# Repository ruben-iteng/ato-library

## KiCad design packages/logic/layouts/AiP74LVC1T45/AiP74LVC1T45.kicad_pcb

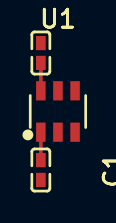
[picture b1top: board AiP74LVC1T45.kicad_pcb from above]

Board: 2 copper layers, 3 parts (0 on the bottom side), 3 nets.

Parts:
C1, C2: 100nF ±10% 16V X7R; C0402-b3ef17
U1: SOT-23-6_L2.9-W1.6-P0.95-LS2.8-BL-d2c740

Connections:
gnd: C1.2, C2.2, U1.2
hv: C1.1, U1.1
hv-1: C2.1, U1.6

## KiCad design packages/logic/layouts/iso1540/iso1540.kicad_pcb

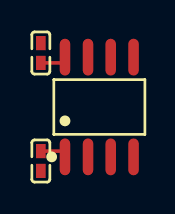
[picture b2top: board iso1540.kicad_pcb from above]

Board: 2 copper layers, 3 parts (0 on the bottom side), 4 nets.

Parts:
C1, C2: 100nF ±10% 16V X7R; C0402-b3ef17
U1: SOIC-8_L4.9-W3.9-P1.27-LS6.0-BL-6ccfeb

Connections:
gnd: C2.2, U1.4
gnd-1: C1.2, U1.5
hv: C2.1, U1.1
hv-1: C1.1, U1.8
